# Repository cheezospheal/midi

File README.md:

# MIDI
A custom PCB designed to play melodies on a keypad, switch to different octaves, and includes a screen that shows what note you're playing!

While I've never been too interested in music (I'm very musically illiterate and got absolutely terrible marks in all of my music classes), I AM interested in hardware. I tried to make my MIDI very not-music-focused, or at least, very simple so even people like me can understand. A MIDI is essentially an instrument that that does not literally emit sound, but rather transmits to the computer what to play. It's also a little more complex than just a PCB with an OLED, so I get to use some more of my PCB designing skills and practice making something completely new! It being interactive as well opens up a lot more possibilities for what I can do with the PCB, and I tried to make it as custom as I can with my current skill level. 

## Features
* 7 capacitive touch keys that correspond to the 7 notes of a C Major Scale
* 5 RGB LED lights that cycle through an animation
* A mod wheel in a potentiometer slider for adding filters/expression
* A volume change potentiometer slider
* 2 key switches that allow for changing the octave [Custom]
* 1 key switch that plays a kick drum
* An OLED that will display what note is being played [Custom]
  
## Summary
The PCB and schematic were designed in **KiCad** and the firmware was coded in **VS Code** (in advance) using **KMK** and **CircuitPython**. Please see the files below to import what you need into the respective softwares.

### General Files
|File|What's Inside?|
|---|---|
|midi.kicad_pcb|contains the PCB layout, including the footprints, footprints, and edge cuts|
|midi.kicad_pro|contains the project settings and configuration|
|midi.kicad_sch|contains the schematic and connections|
|midi_gerbers.zip|contains several gerber files|
|code.py|contains the firmware used to run the microcontroller|

### External Libraries
There are several libraries that are also needed to run the firmware! Please download the following files from the following links:
|File/Folder|What does it do?|Link|
|---|---|---|
|adafruit_displayio_ssd1306.mpy|contains info for CircuitPython on how to initialize the OLED and draw pixels|https://github.com/adafruit/Adafruit_CircuitPython_Bundle/releases (Extract from the lib folder in the bundle)|
|adafruit_display_text|allows the OLED to display texts and fonts|https://github.com/adafruit/Adafruit_CircuitPython_Bundle/releases (Extract from the lib folder in the bundle)|
|adafruit_midi|contains standard MIDI info, functions, and data|https://github.com/adafruit/Adafruit_CircuitPython_Bundle/releases (Extract from the lib folder in the bundle)|
|kmk|firmware for use with CircuitPython specifically for custom keyboards and MIDIs|https://github.com/KMKfw/kmk_firmware|

## Schematic
The schematic is located inside the midi.kicad_sch file, and you'll notice some parts of interest. 
* [U1] Waveshare ESP32-S3-ZERO (microcontroller)
* [SW_1, SW_2, SW_3] SW_Push (tactile push switches)
* [RV1, RV2] R_Potentiometer_MountingPin (slider potentiometers)
* [J1] Conn_01x07_Pin (connecting pins for the capacitive touch keys)
* [J2] Conn_o1x04_Pin (connecting pins for the OLED)
* [D1, D2, D3, D4, D5] SK6812MINI-E (RGB LEDs)
* [R1] 330 (330 Ohm Resistor)

Use the pins as reference for the firmware later on!
|GPIO|Component|Part|
|---|---|---|
|GPIO1|I2C SCL|OLED|
|GPIO2|I2C SDA|OLED|
|GPIO3|SLIDE1|Potentiometer RV1|
|GPIO4|Slide2|Potentiometer RV2|
|GPIO5|LED|RGB LEDs|
|GPIO6|SWITCH3|Tactile Push Switch SW3|
|GPIO7|TOUCH7|Capacitive Touch Keys|
|GPIO8|TOUCH6|Capacitive Touch Keys|
|GPIO9|TOUCH5|Capacitive Touch Keys|
|GPIO10|TOUCH4|Capacitive Touch Keys|
|GPIO11|TOUCH3|Capacitive Touch Keys|
|GPIO12|TOUCH2|Capacitive Touch Keys|
|GPIO13|TOUCH1|Capacitive Touch Keys|
|GPIO43|SWITCH1|Tactile Push Switch SW1|
|GPIO44|SWITCH2|Tactile Push Switch SW2|

## Routing & Customization
Open up the .kicad_pcb file to see the PCB in the editor! The routing was made using both F.cu and B.cu layers, with vias to connect them. I also added a GND pour, so I don't have to route any of the GND ratlines on the back. However, make sure you don't include the GND pour on the capacitive touch keys! The image graphics were added using KiCad's built in image converter, where you can upload any image and it will automatically convert into a black and white bitmap for you to add. Then, just add it in as a footprint (you may need your own .pretty library for this) and edit it to be on the F.Silkscreen layer in the footprint editor. The text is much simpler, just use KiCad's built in text function and write your text! KiCad has multiple fonts to use, so I used Wingdings and Bell MT. If you want to see how your PCB will probably eventually look like, you can open it up in the 3D Viewer! 

## Firmware
(For Half Life, I used the MIDI tutorial's firmware as a base)
Open up the code.py file in VS Code if you want to edit it in advance (if you don't have your physical PCB yet) or you can connect the microcontroller via USB to your computer.

#### Setup
```python
import keypad
import touchio
import busio
import terminalio
import displayio
import adafruit_displayio_ssd1306
from adafruit_midi.control_change import ControlChange
from microcontroller import pin

from kmk.extensions.media_keys import MediaKeys
from kmk.extensions.rgb import RGB, AnimationModes
from kmk.keys import KC
from kmk.kmk_keyboard import KMKKeyboard
from kmk.modules.midi import MidiKeys
from kmk.modules.potentiometer import PotentiometerHandler
from kmk.scanners import Scanner
from kmk.scanners.keypad import KeysScanner
from adafruit_display_text import label
from adafruit_displayio_ssd1306 import SSD1306
```
The first part of the code imports the tools we need from specific libraries, which need to be downloaded (see External Libraries). The io libraries are built in, so no need to download those.

#### Touch Scanner
```python
class TouchScanner(Scanner):
    def __init__(self, pins):
        self.pads = [touchio.TouchIn(p) for p in pins]
        self.pressed = [False] * len(pins)

    @property
    def key_count(self):
        return len(self.pads)

    def scan_for_changes(self):
        for i, pad in enumerate(self.pads):
            touched = pad.value
            if touched != self.pressed[i]:
                self.pressed[i] = touched
                if touched:
                    note_label.text = NOTE_NAMES[i]
                else:
                    note_label.text = "-"
                return keypad.Event(i + self.offset, touched)
```

This part of the code is a touch scanner for the capacitive touch keys, which can detect which key is pressed and whether it is pressed or not. The if statement inside the if touched != self.pressed[i] was added by me, and it is the part that displays what note is being played on the OLED (explained in more detail below). 

#### OLED
```python
keyboard = KMKKeyboard()
# These have to be created before we use KC.MIDI_NOTE / KC.VOLU below
midi = MidiKeys()
media_keys = MediaKeys()
displayio.release_displays()
i2c = busio.I2C(scl=pin.GPIO1, sda=pin.GPIO2)
# setup for OLED! 
display_bus = displayio.I2CDisplay(i2c, device_address=0x3C)
display = adafruit_displayio_ssd1306.SSD1306(display_bus, width=128, height=64)

# OLED stuff
screen_group = displayio.Group()
display.show(screen_group)
note_label = label.Label(terminalio.FONT, text = "-", scale=3, x=52, y=32)
screen_group.append(note_label)
NOTE_NAMES = ["C", "D", "E", "F", "G", "A", "B"]
```  
This is the setup for the different components of the MIDI, such as the keys, volume change, and the OLED. The OLED needs to have the i2c labeled, the address given, and the dimensions configured. In the OLED stuff section, there'll be the actual firmware for how the OLED detects what to display (coded by me!). It uses a label that refers to a set called NOTE_NAMES. When a note isn't playing, it will just display "-", but when it is, it will use the index from the touch keys (for what number key is playing) and refer to the set (C, D, E, F, G, A, B), with indexes from 0 to 6 referring to each note respectively. 

#### Pin Numbers
```python
keyboard.matrix = [
    # Touch pads 1-7 (keys 0-6)
    TouchScanner([pin.GPIO13, pin.GPIO12, pin.GPIO11, pin.GPIO10, pin.GPIO9, pin.GPIO8, pin.GPIO7]),
    # Switches SW1-SW3 (keys 7-9)
    KeysScanner([pin.GPIO6, pin.GPIO43, pin.GPIO44], value_when_pressed=False, pull=True),
]
```
This is where all the GPIO pins are referenced, so if you are updating the pins make sure to update the firmware as well! <br>

#### Octave Change
```python
# Touch pads play a C major scale, switch 1 changes octave up, switch 2 changes octave down, switch 3 plays a kick drum.
keyboard.keymap = [[
    # Normal octave
    KC.MIDI_NOTE(60), KC.MIDI_NOTE(62), KC.MIDI_NOTE(64), KC.MIDI_NOTE(65),
    KC.MIDI_NOTE(67), KC.MIDI_NOTE(69), KC.MIDI_NOTE(71),
    KC.MO(1),
    KC.MO(2),
    KC.MIDI_NOTE(36),
],
    # Higher octave
[
    KC.MIDI_NOTE(72), KC.MIDI_NOTE(74), KC.MIDI_NOTE(76), KC.MIDI_NOTE(77),
    KC.MIDI_NOTE(79), KC.MIDI_NOTE(81), KC.MIDI_NOTE(83),
    KC.TRNS,
    KC.TRNS,
    KC.TRNS,
],
    # Lower octave
[
    KC.MIDI_NOTE(48), KC.MIDI_NOTE(50), KC.MIDI_NOTE(52), KC.MIDI_NOTE(53),
    KC.MIDI_NOTE(55), KC.MIDI_NOTE(57), KC.MIDI_NOTE(59),
    KC.TRNS,
    KC.TRNS,
    KC.TRNS,

]]
```
This is another custom section that that changes the octave of each key when the first and second switch are pressed, then switches back to the normal octave when they are let go. What is important to note is that the switch doesn't actually make the note change octaves, but rather plays an entirely new note. You probably won't notice this, though, unless you look at the firmware >:) 

The code works in layers, where there is a normal layer, a higher octave layer, and a lower octave layer. The first bunch of lines refers to the notes played at the normal octave, the second bunch refers to the higher octave, and the third bunch refers to the lower octave. There are 7 KC.MIDI_NOTE(#), which refer to each note played when a touch key is pressed. The three lines following those refer to the functions of the switches. The first and second buttons switch to the higher and lower layers respectively, and the third switch plays a kick drum (it also uses KC.MIDI_NOTE). 

#### Sliders, RGB Lights
```python
# Sliders send MIDI CC 1 (mod wheel) and CC 7 (volume)
sliders = PotentiometerHandler()
sliders.pins = (
    (pin.GPIO3, lambda state: midi.send(ControlChange(1, state.position))),
    (pin.GPIO4, lambda state: midi.send(ControlChange(7, state.position))),
)

keyboard.modules = [midi, sliders]
keyboard.extensions = [
    media_keys,
    RGB(pixel_pin=pin.GPIO5, num_pixels=5, val_default=80, animation_mode=AnimationModes.BREATHE_RAINBOW),
]

if __name__ == '__main__':
    keyboard.go()
```
This final area of code is for the rest of the functions (sliders, RGB lights), and was left mostly unchanged. The one thing I did change though was the animation playing on the RGB lights (changed to RAINBOW_BREATHE), since I thought it might look cooler.

## Bill of Materials
Please note that this BOM is for general users! For Half Life, please view the BOM submitted on the Half Life website. Also note that these prices are given without any special discounts, but AliExpress often gives discounts anyways, so prices are probably cheaper than shown. Shipping is based off my own address and the tax is calculated with the Ontario rate of 13%. 

|Part|Price (USD)|Quantity Used|Vendor|Link|
|---|---|---|---|---|
|PCB|$12.70|1|JLCPCB|https://jlcpcb.com/|
|Waveshare ESP32-S3-ZERO|$3.56|1|AliExpress|https://www.aliexpress.com/item/1005007948911104.html?src=google&src=google&albch=shopping&acnt=677-394-9260&isdl=y&slnk=&plac=&mtctp=&albbt=Google_7_shopping&aff_platform=google&aff_short_key=_oFgTQeV&gclsrc=aw.ds&albagn=888888&ds_e_adid=&ds_e_matchtype=&ds_e_device=c&ds_e_network=x&ds_e_product_group_id=&ds_e_product_id=en1005007948911104&ds_e_product_merchant_id=5851714237&ds_e_product_country=CA&ds_e_product_language=en&ds_e_product_channel=online&ds_e_product_store_id=&ds_url_v=2&albcp=23838573336&albag=&isSmbAutoCall=false&needSmbHouyi=false&gad_source=1&gad_campaignid=23843844140&gbraid=0AAAABCtupDPue3-xCwmVvJcb3nqWDDgmn&gclid=Cj0KCQjwrvHWBhDKARIsABmp7h1pBcGAcLLLmYV95D3AN_8gVdcy4el_jwCGC9PHR4R6y6rGWIvplrwaAn7eEALw_wcB|
|SK6812 RGB LEDs|$2.61|1|AliExpress|[https://www.aliexpress.com/item/1005007863635868.html?spm=a2g0o.productlist.main.1.467e66echpig2D&algo_pvid=17f43b4a-c6ec-4e01-9861-3f38f1696518&algo_exp_id=17f43b4a-c6ec-4e01-9861-3f38f1696518-0&pdp_ext_f=%7B%22order%22%3A%22641%22%2C%22eval%22%3A%221%22%2C%22fromPage%22%3A%22search%22%7D&pdp_npi=6%40dis%21CAD%216.71%211.42%21%21%214.68%210.99%21%402101c69517929046052793291e0d52%2112000042594617264%21sea%21CA%218338085966%21ABX%211%210%21n_tag%3A-29910%3Bd%3Ac42caa26%3Bm03_new_user%3A-29895%3BpisId%3A5000000218625932&curPageLogUid=AQFVQ5jQSkKF&utparam-url=scene%3Asearch%7Cquery_from%3A%7Cx_object_id%3A1005007863635868%7C_p_origin_prod%3A](https://www.aliexpress.com/item/1005005193716172.html?spm=a2g0o.cart.0.0.69e838dal0d3wx&mp=1&pdp_npi=6%40dis%21CAD%21CAD+3.65%21CAD+3.65%21%21CAD+3.65%21%21%21%402101ea8f17929799530491274e077e%2112000032072424633%21ct%21CA%218338085966%21%211%210%21)|
|330Ω Resistor|$2.11|1|Sayal Electronics|https://secure.sayal.com/STORE4/prodetails.php?SKU=198449|
|Bourns 15mm Slide Potentiometer|$1.95|2|Digikey|https://www.digikey.ca/en/products/detail/bourns-inc/PTA1543-2010CIB103/3781161|
|Low Choc Kailh Key Switches|$7.99|1|AliExpress|https://www.aliexpress.com/item/1005008883418065.html?spm=a2g0o.productlist.main.1.1c9e5913F8kBSt&algo_pvid=278c7c25-9ab1-4a2a-9760-88be0dc0cf20&algo_exp_id=278c7c25-9ab1-4a2a-9760-88be0dc0cf20-0&pdp_ext_f=%7B%22order%22%3A%221409%22%2C%22spu_best_type%22%3A%22price%22%2C%22eval%22%3A%221%22%2C%22fromPage%22%3A%22search%22%7D&pdp_npi=6%40dis%21CAD%2111.19%212.96%21%21%217.81%212.07%21%402101c69517929071229613399e0f00%2112000047082945007%21sea%21CA%218338085966%21ABX%211%210%21n_tag%3A-29910%3Bd%3Ac42caa26%3Bm03_new_user%3A-29895%3BpisId%3A5000000218625932&curPageLogUid=Vd6zfVEWhxYp&utparam-url=scene%3Asearch%7Cquery_from%3A%7Cx_object_id%3A1005008883418065%7C_p_origin_prod%3A|
|Low Choc Kailh Key Caps|$4.35|1|AliExpress|[https://www.aliexpress.com/item/1005009278324475.html?spm=a2g0o.productlist.main.7.44362d34xEB8gR&algo_pvid=9f630577-147e-4a07-a9a7-5f5d71948c36&algo_exp_id=9f630577-147e-4a07-a9a7-5f5d71948c36-6&pdp_ext_f=%7B%22order%22%3A%22173%22%2C%22eval%22%3A%221%22%2C%22fromPage%22%3A%22search%22%7D&pdp_npi=6%40dis%21CAD%217.65%211.42%21%21%215.34%210.99%21%402101dedf17929083063836626e0f26%2112000048589993989%21sea%21CA%218338085966%21ABX%211%210%21n_tag%3A-29910%3Bd%3Ac42caa26%3Bm03_new_user%3A-29895%3BpisId%3A5000000218625932&curPageLogUid=x2W0Y7VzQsWN&utparam-url=scene%3Asearch%7Cquery_from%3A%7Cx_object_id%3A1005009278324475%7C_p_origin_prod%3A](https://www.aliexpress.com/item/1005006734545486.html?spm=a2g0o.cart.0.0.69e838dal0d3wx&mp=1&pdp_npi=6%40dis%21CAD%21CAD+6.09%21CAD+6.09%21%21CAD+6.09%21%21%21%402101ea8f17929799530491274e077e%2112000044697706461%21ct%21CA%218338085966%21%211%210%21&pdp_ext_f=%7B%22cart2PdpParams%22%3A%7B%22pdpBusinessMode%22%3A%22retail%22%7D%7D)|
|96" 128 x 64 OLED|$2.73|1|AliExpress|https://www.aliexpress.com/item/1005006141235306.html?spm=a2g0o.cart.0.0.69e838dal0d3wx&mp=1&pdp_npi=6%40dis%21CAD%21CAD+3.82%21CAD+3.82%21%21CAD+3.82%21%21%21%402101ea8f17929799530491274e077e%2112000035944225407%21ct%21CA%218338085966%21%211%210%21|
|Taxes & Shipping|$20.82|-|-|-|
|Total|$60.77|-|-|-|

## Extra Notes [Half Life]
Note that, for the cart screenshots submitted on the Half Life website, all prices are in CAD. However, all prices have been converted for each individual item into USD for the BOM, thus there may be a small rounding error (will most likely be negligible; I can pay the difference out of pocket). Furthermore, there are special discounts (specifically for AliExpress) located in the BOM.csv from Half Life, which is why I am able to afford it under the $30 budget. For DigiKey, I am also only getting the shipping cost with the grant, not the part cost. Additionally, for providing the grant, please look at the BOM submitted on Half Life, not the BOM.csv here (as the BOM on Half Life is under $30).

Please pay attention to the descriptions of each item! Those that are labeled with [OUT OF POCKET] and [ALREADY OWNED] are not purchased with the grant and thus cost $0.01. Additionally, the vendors labeled (Local) are local to me, so I do not have to pay for shipping as I can go to them in person. All shipping prices are based on my own address and ability to go in-person for certain vendors.

I'm really proud of my MIDI and I hope you are too! While I'm no expert in PCBs, I've at least made a lot more progress and was able to add more custom features than I did with my Starbie. Good luck with reviewing!

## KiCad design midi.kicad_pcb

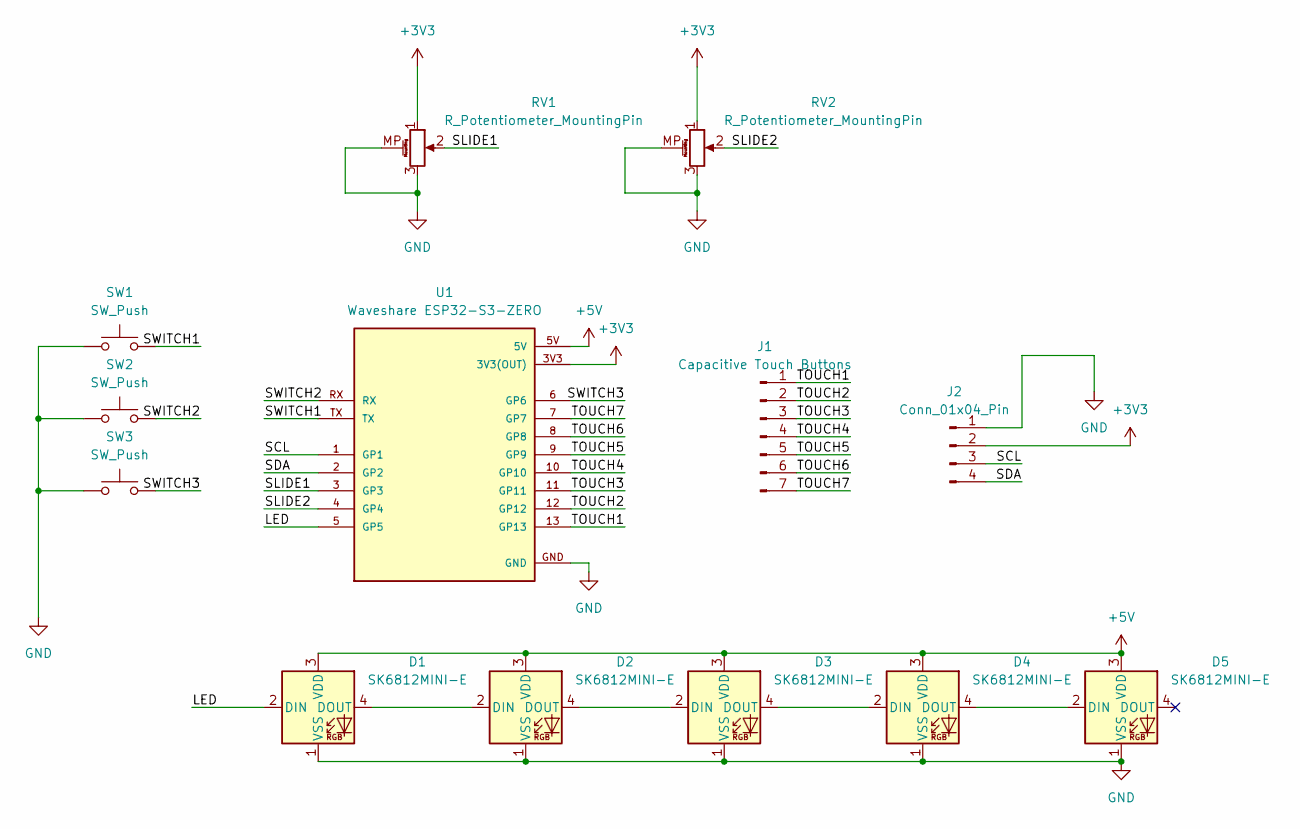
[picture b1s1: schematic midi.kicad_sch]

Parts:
D1, D2, D3, D4, D5: SK6812MINI-E; LED_SK6812MINI-E_3.2x2.8mm_P1.5mm_ReverseMount
J1: Capacitive Touch Buttons; Star_7_Keys
J2: Conn_01x04_Pin; FanPinHeader_1x04_P2.54mm_Vertical
RV1, RV2: R_Potentiometer_MountingPin; Potentiometer_Bourns_PTA1543_Single_Slide
SW1, SW2, SW3: SW_Push; Kailh Choc Low-Profile Switches
U1: Waveshare ESP32-S3-ZERO; Waveshare ESP32-S3-Zero; PARTREV NA

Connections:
+3V3: J2.2, RV1.1, RV2.1, U1.3V3 (3V3(OUT))
+5V: D1.3 (VDD), D2.3 (VDD), D3.3 (VDD), D4.3 (VDD), D5.3 (VDD), U1.5V
/LED: D1.2 (DIN), U1.5 (GP5)
/SCL: J2.3, U1.1 (GP1)
/SDA: J2.4, U1.2 (GP2)
/SLIDE1: RV1.2, U1.3 (GP3)
/SLIDE2: RV2.2, U1.4 (GP4)
/SWITCH1: SW1.2, U1.TX
/SWITCH2: SW2.2, U1.RX
/SWITCH3: SW3.2, U1.6 (GP6)
/TOUCH1: J1.1, U1.13 (GP13)
/TOUCH2: J1.2, U1.12 (GP12)
/TOUCH3: J1.3, U1.11 (GP11)
/TOUCH4: J1.4, U1.10 (GP10)
/TOUCH5: J1.5, U1.9 (GP9)
/TOUCH6: J1.6, U1.8 (GP8)
/TOUCH7: J1.7, U1.7 (GP7)
GND: D1.1 (VSS), D2.1 (VSS), D3.1 (VSS), D4.1 (VSS), D5.1 (VSS), J2.1, RV1.3, RV1.MP (MountPin), RV2.3, RV2.MP (MountPin), SW1.1, SW2.1, SW3.1, U1.GND
unnamed: D1.4 (DOUT), D2.2 (DIN)
unnamed: D2.4 (DOUT), D3.2 (DIN)
unnamed: D3.4 (DOUT), D4.2 (DIN)
unnamed: D4.4 (DOUT), D5.2 (DIN)

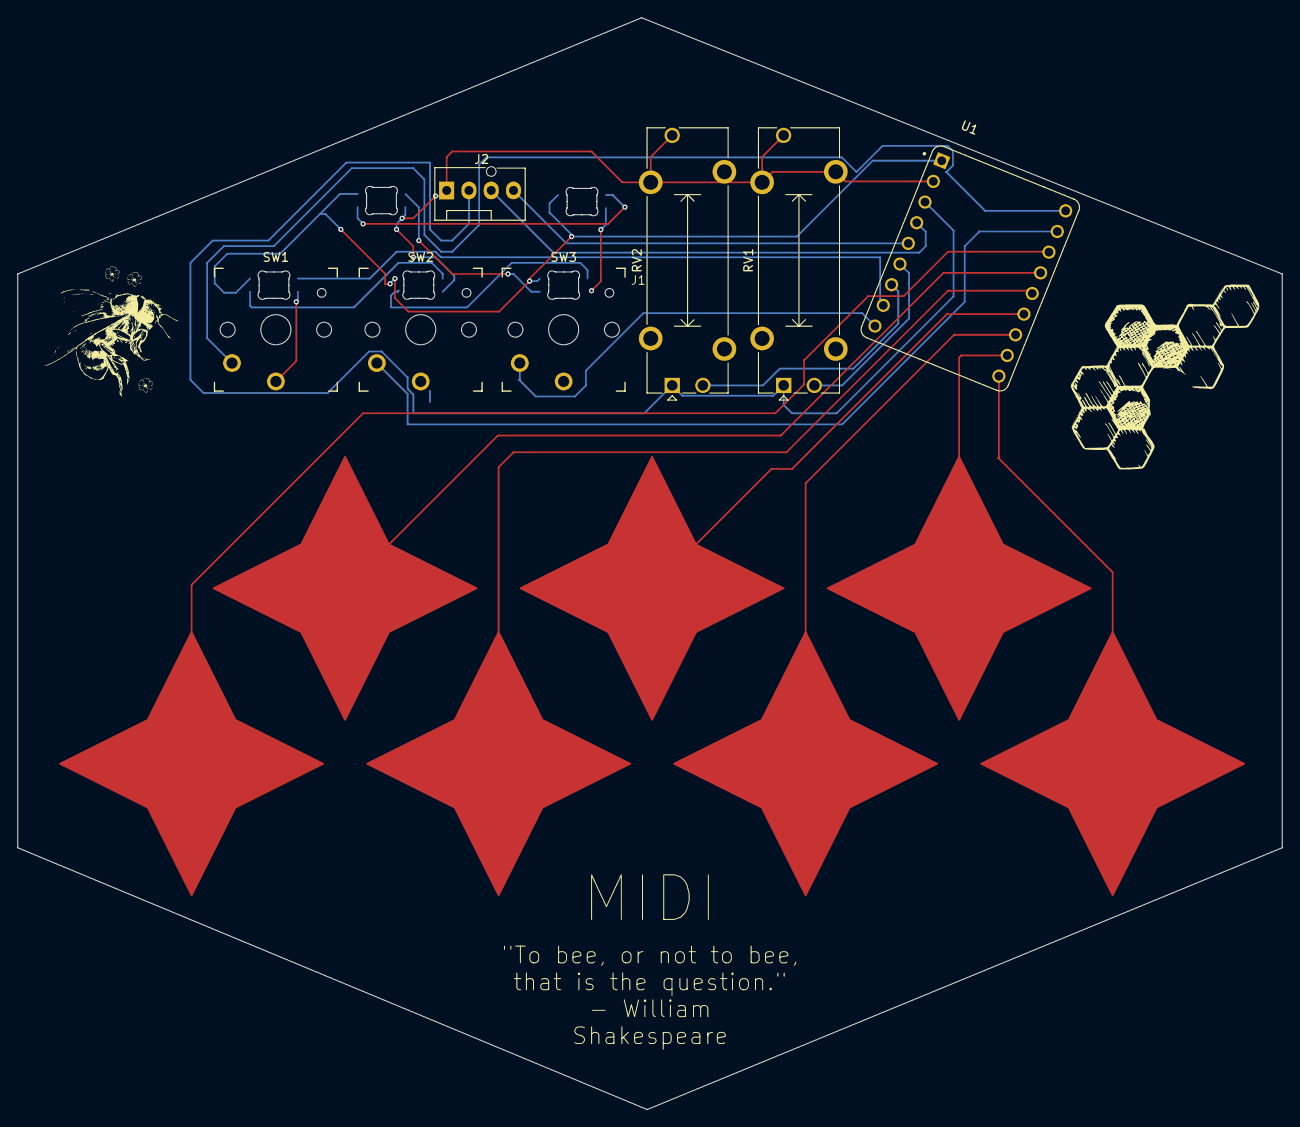
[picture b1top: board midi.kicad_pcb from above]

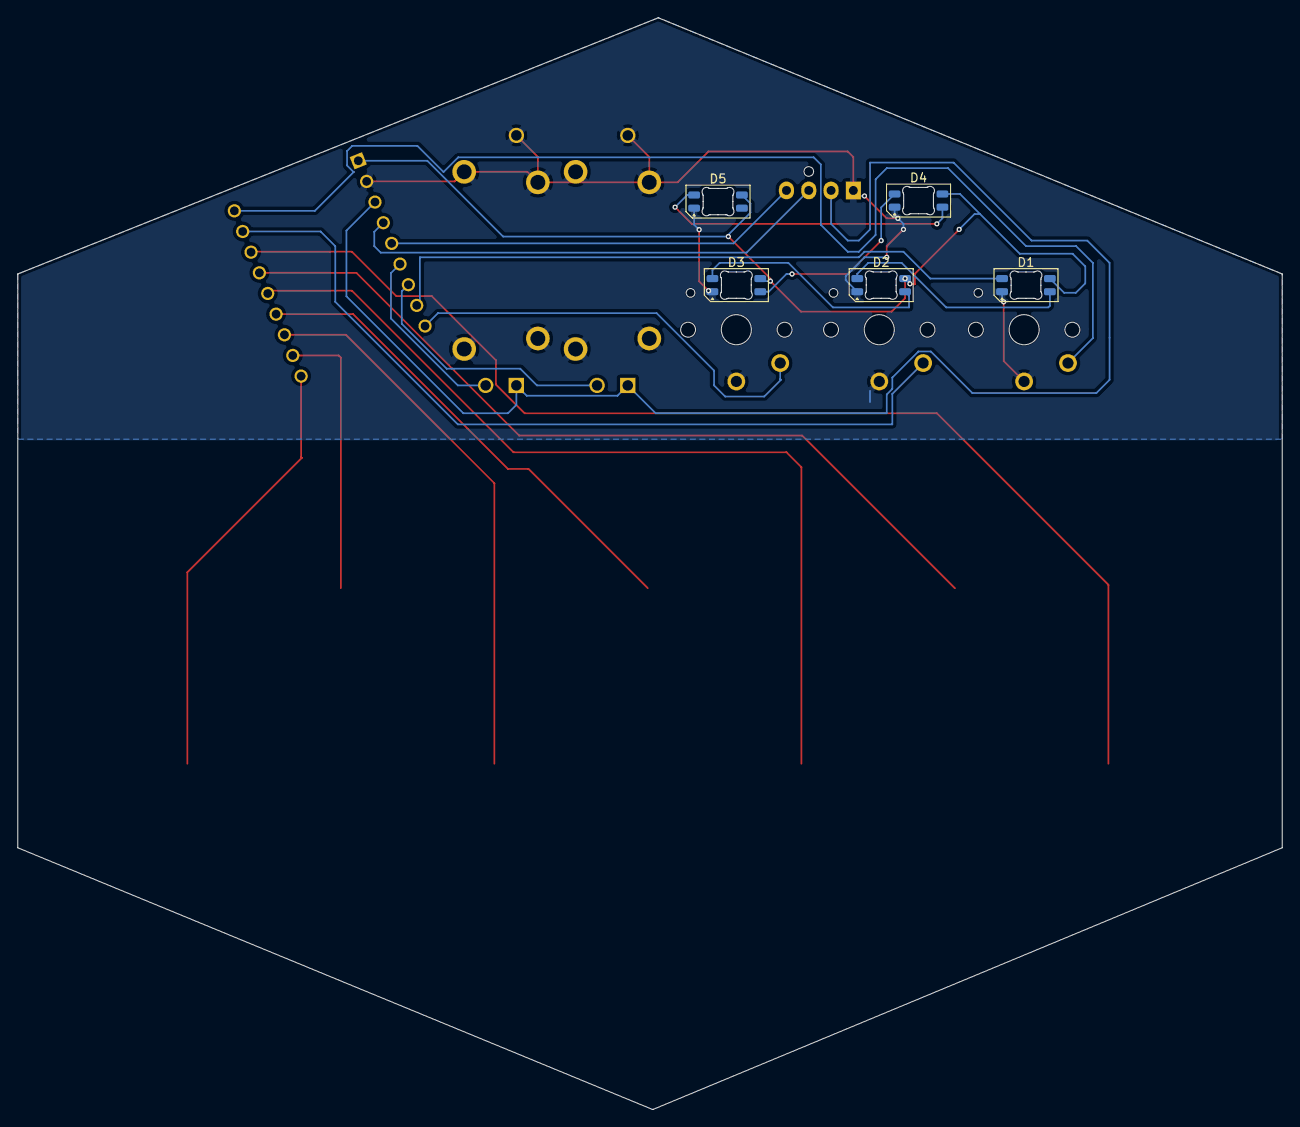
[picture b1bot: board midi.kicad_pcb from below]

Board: 2 copper layers, 144.1 x 124.5 mm, 13 parts (5 on the bottom side), 22 nets.
